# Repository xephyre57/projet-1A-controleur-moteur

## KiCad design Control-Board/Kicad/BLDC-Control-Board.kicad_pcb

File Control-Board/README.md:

# Carte de contrôle

## Objectif

Le but de cette carte de contrôle est de servir de cerveau que l'on vient plugger sur la carte de puissance adaptée au moteur que l'on souhaite contrôler. Cette connexion se fait via un [shield personalisé](#shield-de-connexion) qui permet de faire passer les signaux nécessaires entre les deux cartes ainsi que de les fixer ensemble. 

Cette carte de contrôle a été conçue autour d'un [STSPIN32G4](https://www.st.com/en/motor-drivers/stspin32g4.html) qui présente l'avantage d'avoir à la fois un microcontrôleur et un driver de mofsets intégré dans la même puce. Cela permet de réduire le nombre de composants nécessaires et ainsi d'avoir une carte plus compacte.

## Shématique de la carte de contrôle :

Le schéma de la carte de contrôle est disponible [ici](./Kicad/BLDC-Control-Board.kicad_sch), il a été séparé en 4 parties pour une meilleure lisibilité :
- [MCU & debug](#mcu--debug) : cette partie regroupe le microcontrôleur ainsi que tous les éléments nécessaires pour le faire fonctionner (oscillateur, capacités, pont diviseur de tension pour la programmation, etc.) ainsi que les diodes de debug.
- [Analog Sensing](#analog-sensing) : cette partie est dédiée à l'acquisition des signaux des capteurs de position (hall effect sensors) pour l'asservissement du moteur.
- [Communication](#communication) : cette partie regroupe les éléments nécessaires pour la communication extérieure (I2C, UART et CAN) ainsi que le ST-Link pour la programmation et le debug.
- [Connector](#connector) : cette partie contient les connecteurs et les point de fixation pour le [shield de connexion](#shield-de-connexion).

### MCU & debug

Cette première partie du schéma regroupe le microcontrôleur (en haut à gauche) ainsi que tous les éléments nécessaires pour le faire fonctionner (oscillateur, capacités, pont diviseur de tension pour la programmation, etc.) ainsi que les diodes de debug (en bas à gauche).

Pour le dimensionnement des différents éléments, nous avons suivi les recommandations de STMicroelectronics présentes dans la [datasheet du STSPIN32G4](https://www.st.com/resource/en/datasheet/stspin32g4.pdf) ainsi que dans les [application notes](https://www.st.com/en/motor-drivers/stspin32g4.html#documentation) associées.

### Analog Sensing

Dans cette partie du schéma, le but est de faire l'acquisition des signaux des capteurs de position (hall effect sensors) pour l'asservissement du moteur. Pour ce faire, nous avons utilisé les amplificateurs opérationnels intégrés dans le STSPIN32G4. Les amplificateurs opérationnels visibles sur le schéma si dessus ne sont donc pas des composants externes, ils sont simplement là afin d'aider à la lisibilité du schéma, par ailleurs afin d'éviter des erreurs lors du test du schéma, l'amplificateur opérationnel manquant du groupe de 4 ainsi que l'alimentation de ces amplificateurs opérationnels ont été dessinés dans le cadre en bas à gauche du schéma.

Par ailleurs, on peut remarquer sur le schéma que la boucle de retour sont barrée, sur le schéma, c'est du au fait que le logiciel que nous avons utilisé pour générer un code pour notre carte impose d'utilise une boucle de retour interne, nous n'avons donc pas peuplé ces composants et nous avons juste remplacer la résistance R_OP4_X par une soudure. Il est possible pour une prochaine version de la carte de retirer ces composants du PCB, cependant il peut être intéressant de les laisser car si on ne passe pas par le logiciel que l'on a utilisé pour générer le code, le fait d'avoir une boucle de retour externe permet d'avoir une plus grande flexibilité dans le choix de la configuration de la boucle de retour (la boucle de retour interne ne permet que de faire des puissance de 2).

### Communication

Cette partie du schéma regroupe les éléments lié à la communication extérieure. L'un des points du cahier des charges de cette carte était de faire une carte universelle qui à therme soit systématiquement utilisée lors que l'on a besoin de contrôler un moteur BDLC dans l'école. Dans ce cadre, il est nécessaire que la carte puisse communiquer avec la majorité des systèmes de contrôle, c'est pourquoi nous avons choisi d'intégrer à la fois une communication I2C, UART et CAN. 

D'autre part nous avons également intégré un connecteur pour le ST-Link avec les signaux nécessaires pour la programmation ainsi que ce nécessaire pour le debug afin de faciliter le développement sur la carte.

### Connector

## PCB

Pour le PCB il a été choisit de le faire en 4 couches afin de pouvoir réduire la taille de la carte tout en respectant les règles de routage. Le PCB a été conçu sur kicad et le fichier de conception est disponible [ici](./Kicad/BLDC-Control-Board.kicad_pcb).

### Répartition des couches
- Couches 1 (Top) contient tout les composants (à l'exception du connecteur avec la carte de puissance qui doit être situé sur la couche du dessous) ainsi que la majorité des pistes de signal.
- Couche 2 (GND) Cette couche est dédiée à la masse de la carte, aucune piste ne passe sur cette couche, les seul éléments présent sur cette couche sont le plan de masse ainsi que les vias.
- Couche 3 (Power) Cette couche est dédiée à l'alimentation de la carte, aucun plan de masse ne passe sur cette couche, Les deux circuits d'alimentation principaux de la carte (VM 24-48V et VBAT 3.3V) utilisent des plans d'alimentation sur cette couche plutôt que des pistes par ailleurs.
- Couche 4 (Bottom) Cette couche contient les pistes de signal qui ne pouvaient pas être routé sur la couche du dessus ainsi que le connecteur pour la carte de puissance qui doit être situé sur cette couche afin de pouvoir faire face à la carte de puissance.

### Largeur des pistes

Pour la largeur des pistes, nous avons séparé les pistes en deux catégories : 
- **les pistes de puissance** : cette catégorie regroupe toutes les pistes qui sont connectées au controleur de MOSFETs du STSPIN32G4, pour ces pistes, nous avons utilisé une largeur de 2 centièmes de pouce (0.508mm), cette largeur a été choisit en s'appuyant sur les largeurs de pistes utilisées par STMicroelectronics dans leur carte d'évaluation du STSPIN32G4 ([EVSPIN32G4](https://www.st.com/en/evaluation-tools/evspin32g4.html)). Cependant la largeur de piste est réduite à 1 centièmes de pouce (0.254mm) au abords de la puce car les pins du STSPIN32G4 sont trop rapprochées pour permettre une largeur de 2 centièmes de pouce.
- **les pistes de signal** : cette catégorie regroupe toutes les autre pistes (mise à part les pistes d'alimentation qui sont des plans d'alimentation), pour ces pistes, nous avons utilisé une largeur de 1 centièmes de pouce (0.254mm).

### isolation

Premièrement une isolation minimal de 0.2mm a été imposé entre toutes les pistes et les pads. Par ailleurs des tranchées d'isolation de 0.4mm traversant tout le PCB ont été ajoutées afin de lutter contre les problèmes de parasites. Ces tranchées d'isolation sont présentes entre les pistes de puissance et les pistes de signal ainsi qu'autour de l'oscillateur qui est une source de parasites importante.

Par ailleurs, conformément au recommandations de STMicroelectronics, au niveau du circuit d'alimentation et de régulation du STSPIN32G4, le PCB est vide sur toutes les couches à l'exception de la première couche ou seul les pistes nécessaires sont présentes, et remplacées par des zones afin d'augmenter la largeur des pistes.

### Shield de connexion

Pour créer une carte de puissance compatible avec cette carte de contrôle, il suffit d'utiliser le même connecteur (les signaux situés au même endroit) et de respecter la disposition suivantes pour les trous de fixation et le connecteur :

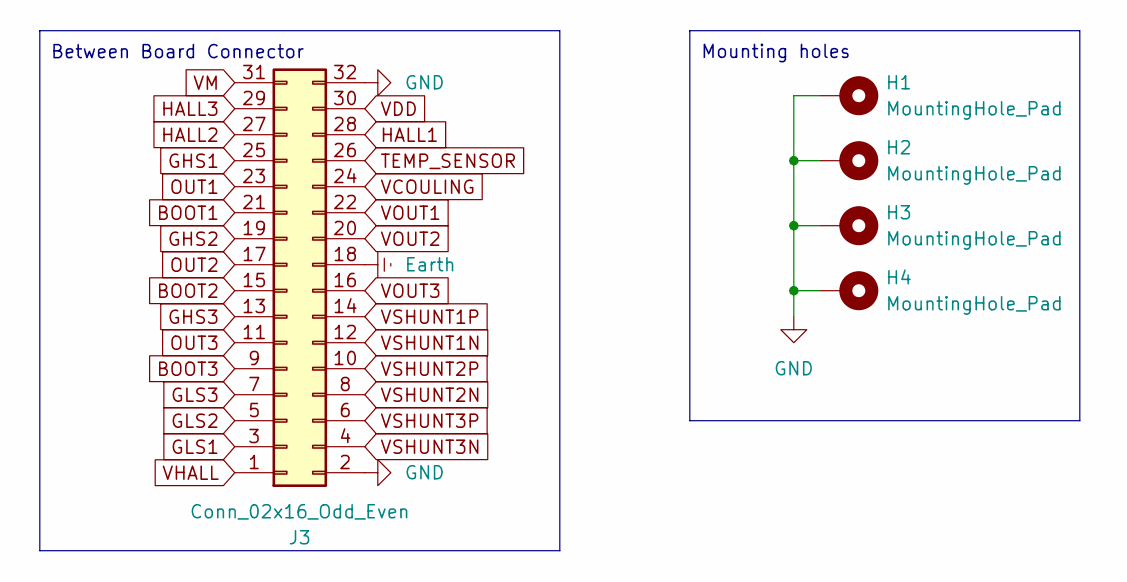
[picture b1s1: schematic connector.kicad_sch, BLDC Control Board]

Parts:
H1, H2, H3, H4: MountingHole_Pad; MountingHole_3.2mm_M3_DIN965_Pad
J3: Conn_02x16_Odd_Even; PinHeader_2x16_P2.54mm_Vertical

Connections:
BOOT1: J3.21; also elsewhere on the board
BOOT2: J3.15; also elsewhere on the board
BOOT3: J3.9; also elsewhere on the board
Earth: H1.1, H2.1, H3.1, H4.1, J3.2, J3.18, J3.32; also elsewhere on the board
GHS1: J3.25; also elsewhere on the board
GHS2: J3.19; also elsewhere on the board
GHS3: J3.13; also elsewhere on the board
GLS1: J3.3; also elsewhere on the board
GLS2: J3.5; also elsewhere on the board
GLS3: J3.7; also elsewhere on the board
HALL1: J3.28; also elsewhere on the board
HALL2: J3.27; also elsewhere on the board
HALL3: J3.29; also elsewhere on the board
OUT1: J3.23; also elsewhere on the board
OUT2: J3.17; also elsewhere on the board
OUT3: J3.11; also elsewhere on the board
TEMP_SENSOR: J3.26; also elsewhere on the board
VBAT: J3.30; also elsewhere on the board
VCOULING: J3.24; also elsewhere on the board
VHALL: J3.1; also elsewhere on the board
VM: J3.31; also elsewhere on the board
VOUT1: J3.22; also elsewhere on the board
VOUT2: J3.20; also elsewhere on the board
VOUT3: J3.16; also elsewhere on the board
VSHUNT1N: J3.12; also elsewhere on the board
VSHUNT1P: J3.14; also elsewhere on the board
VSHUNT2N: J3.8; also elsewhere on the board
VSHUNT2P: J3.10; also elsewhere on the board
VSHUNT3N: J3.4; also elsewhere on the board
VSHUNT3P: J3.6; also elsewhere on the board

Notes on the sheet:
Mounting holes
Between Board Connector

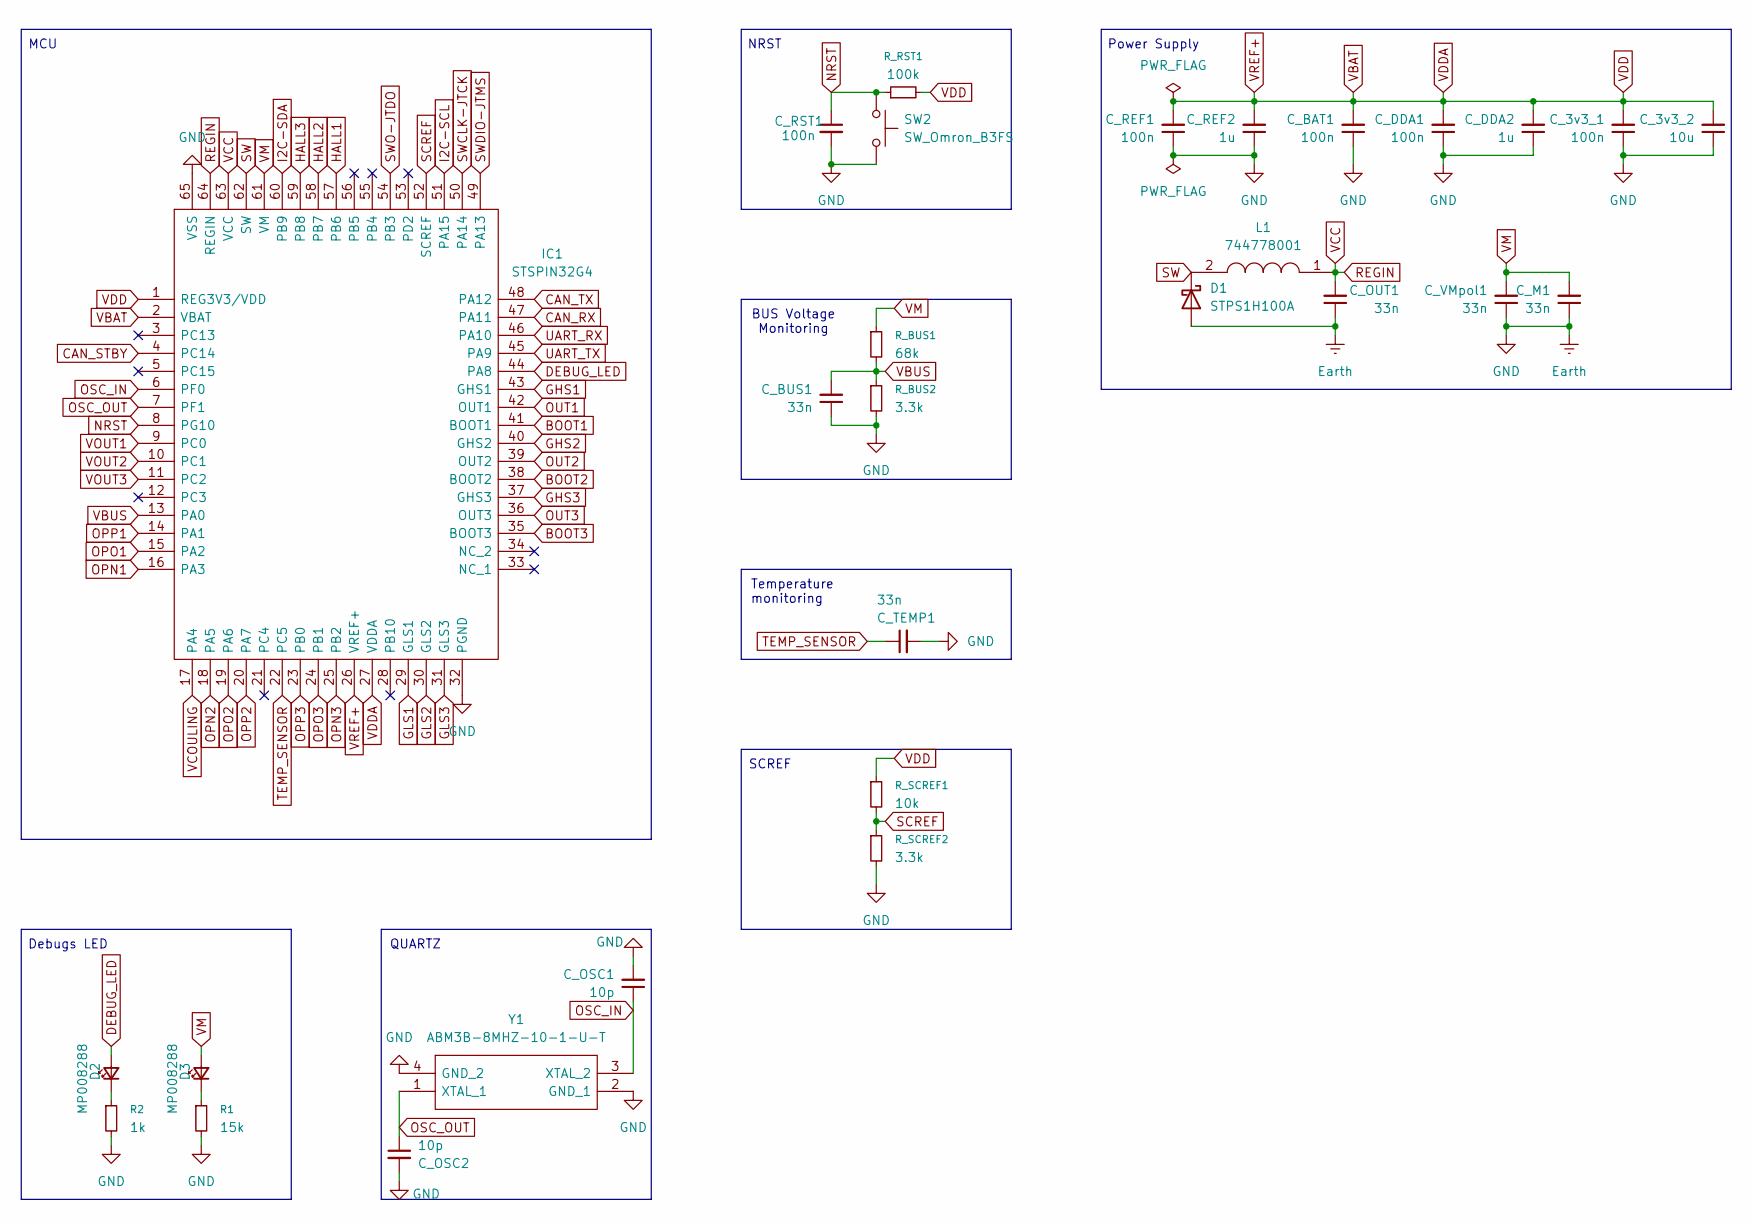
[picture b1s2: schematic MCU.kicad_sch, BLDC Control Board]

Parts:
C_3v3_1: 100n; C_0603_1608Metric_Pad1.08x0.95mm_HandSolder
C_3v3_2: 10u; C_0603_1608Metric_Pad1.08x0.95mm_HandSolder
C_BAT1: 100n; C_0603_1608Metric_Pad1.08x0.95mm_HandSolder
C_BUS1: 33n; C_0603_1608Metric_Pad1.08x0.95mm_HandSolder
C_DDA1: 100n; C_0603_1608Metric_Pad1.08x0.95mm_HandSolder
C_DDA2: 1u; C_0603_1608Metric_Pad1.08x0.95mm_HandSolder
C_M1: 33n; C_0603_1608Metric_Pad1.08x0.95mm_HandSolder
C_OSC1, C_OSC2: 10p; C_0603_1608Metric_Pad1.08x0.95mm_HandSolder
C_OUT1: 33n; C_0603_1608Metric_Pad1.08x0.95mm_HandSolder
C_REF1: 100n; C_0603_1608Metric_Pad1.08x0.95mm_HandSolder
C_REF2: 1u; C_0603_1608Metric_Pad1.08x0.95mm_HandSolder
C_RST1: 100n; C_0603_1608Metric_Pad1.08x0.95mm_HandSolder
C_TEMP1: 33n; C_0603_1608Metric_Pad1.08x0.95mm_HandSolder
C_VMpol1: 33n; C_0603_1608Metric_Pad1.08x0.95mm_HandSolder
D1: STPS1H100A; DIOM5126X265N
D2, D3: MP008288; LED_0603_1608Metric_Pad1.05x0.95mm_HandSolder
IC1: STSPIN32G4; QFN50P900X900X100-65N-D; Manufacturer_Part_Number STSPIN32G4; Mouser Part Number 511-STSPIN32G4
L1: 744778001; Manufacturer_Part_Number 744778001; Mouser Part Number 710-744778001
R1: 15k; R_0603_1608Metric_Pad0.98x0.95mm_HandSolder
R2: 1k; R_0603_1608Metric_Pad0.98x0.95mm_HandSolder
R_BUS1: 68k; R_0603_1608Metric_Pad0.98x0.95mm_HandSolder
R_BUS2: 3.3k; R_0603_1608Metric_Pad0.98x0.95mm_HandSolder
R_RST1: 100k; R_0603_1608Metric_Pad0.98x0.95mm_HandSolder
R_SCREF1: 10k; R_0603_1608Metric_Pad0.98x0.95mm_HandSolder
R_SCREF2: 3.3k; R_0603_1608Metric_Pad0.98x0.95mm_HandSolder
SW2: SW_Omron_B3FS; SW_SPST_Omron_B3FS-100xP
Y1: ABM3B-8MHZ-10-1-U-T; ABM3B; Manufacturer_Part_Number ABM3B-11.0592MHZ-10-1-U-T; Mouser Part Number 815-ABM3B-11.0592-T

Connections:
BOOT1: IC1.41 (BOOT1); also elsewhere on the board
BOOT2: IC1.38 (BOOT2); also elsewhere on the board
BOOT3: IC1.35 (BOOT3); also elsewhere on the board
CAN_RX: IC1.47 (PA11); also elsewhere on the board
CAN_STBY: IC1.4 (PC14); also elsewhere on the board
CAN_TX: IC1.48 (PA12); also elsewhere on the board
DEBUG_LED: D2.2 (A), IC1.44 (PA8)
Earth: C_3v3_1.1, C_3v3_2.1, C_BAT1.1, C_BUS1.1, C_DDA1.1, C_DDA2.1, C_M1.1, C_OSC1.2, C_OSC2.2, C_OUT1.1, C_REF1.1, C_REF2.1, C_RST1.2, C_TEMP1.2, C_VMpol1.1, D1.2 (A), IC1.32 (PGND), IC1.65 (VSS), R1.2, R2.2, R_BUS2.2, R_SCREF2.2, SW2.2, Y1.2 (GND_1), Y1.4 (GND_2); also elsewhere on the board
GHS1: IC1.43 (GHS1); also elsewhere on the board
GHS2: IC1.40 (GHS2); also elsewhere on the board
GHS3: IC1.37 (GHS3); also elsewhere on the board
GLS1: IC1.29 (GLS1); also elsewhere on the board
GLS2: IC1.30 (GLS2); also elsewhere on the board
GLS3: IC1.31 (GLS3); also elsewhere on the board
HALL1: IC1.57 (PB6); also elsewhere on the board
HALL2: IC1.58 (PB7); also elsewhere on the board
HALL3: IC1.59 (PB8); also elsewhere on the board
I2C-SCL: IC1.51 (PA15); also elsewhere on the board
I2C-SDA: IC1.60 (PB9); also elsewhere on the board
NRST: C_RST1.1, IC1.8 (PG10), R_RST1.1, SW2.1; also elsewhere on the board
unnamed: D2.1 (K), R2.1
unnamed: D3.1 (K), R1.1
OPN1: IC1.16 (PA3); also elsewhere on the board
OPN2: IC1.18 (PA5); also elsewhere on the board
OPN3: IC1.25 (PB2); also elsewhere on the board
OPO1: IC1.15 (PA2); also elsewhere on the board
OPO2: IC1.19 (PA6); also elsewhere on the board
OPO3: IC1.24 (PB1); also elsewhere on the board
OPP1: IC1.14 (PA1); also elsewhere on the board
OPP2: IC1.20 (PA7); also elsewhere on the board
OPP3: IC1.23 (PB0); also elsewhere on the board
OSC_IN: C_OSC1.1, IC1.6 (PF0), Y1.3 (XTAL_2)
OSC_OUT: C_OSC2.1, IC1.7 (PF1), Y1.1 (XTAL_1)
OUT1: IC1.42 (OUT1); also elsewhere on the board
OUT2: IC1.39 (OUT2); also elsewhere on the board
OUT3: IC1.36 (OUT3); also elsewhere on the board
REGIN: C_OUT1.2, IC1.63 (VCC), IC1.64 (REGIN), L1.1; also elsewhere on the board
SCREF: IC1.52 (SCREF), R_SCREF1.2, R_SCREF2.1
SW: D1.1 (K), IC1.62 (SW), L1.2
SWCLK-JTCK: IC1.50 (PA14); also elsewhere on the board
SWDIO-JTMS: IC1.49 (PA13); also elsewhere on the board
SWO-JTDO: IC1.54 (PB3); also elsewhere on the board
TEMP_SENSOR: C_TEMP1.1, IC1.22 (PC5); also elsewhere on the board
UART_RX: IC1.46 (PA10); also elsewhere on the board
UART_TX: IC1.45 (PA9); also elsewhere on the board
VBAT: C_3v3_1.2, C_3v3_2.2, C_BAT1.2, C_DDA1.2, C_DDA2.2, C_REF1.2, C_REF2.2, IC1.1 (REG3V3/VDD), IC1.2 (VBAT), IC1.26 (VREF+), IC1.27 (VDDA), R_RST1.2, R_SCREF1.1; also elsewhere on the board
VBUS: C_BUS1.2, IC1.13 (PA0), R_BUS1.2, R_BUS2.1
VCOULING: IC1.17 (PA4); also elsewhere on the board
VM: C_M1.2, C_VMpol1.2, D3.2 (A), IC1.61 (VM), R_BUS1.1; also elsewhere on the board
VOUT1: IC1.9 (PC0); also elsewhere on the board
VOUT2: IC1.10 (PC1); also elsewhere on the board
VOUT3: IC1.11 (PC2); also elsewhere on the board

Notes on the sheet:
QUARTZ
NRST
BUS Voltage Monitoring
Debugs LED
Power Supply
SCREF
MCU
Temperature monitoring

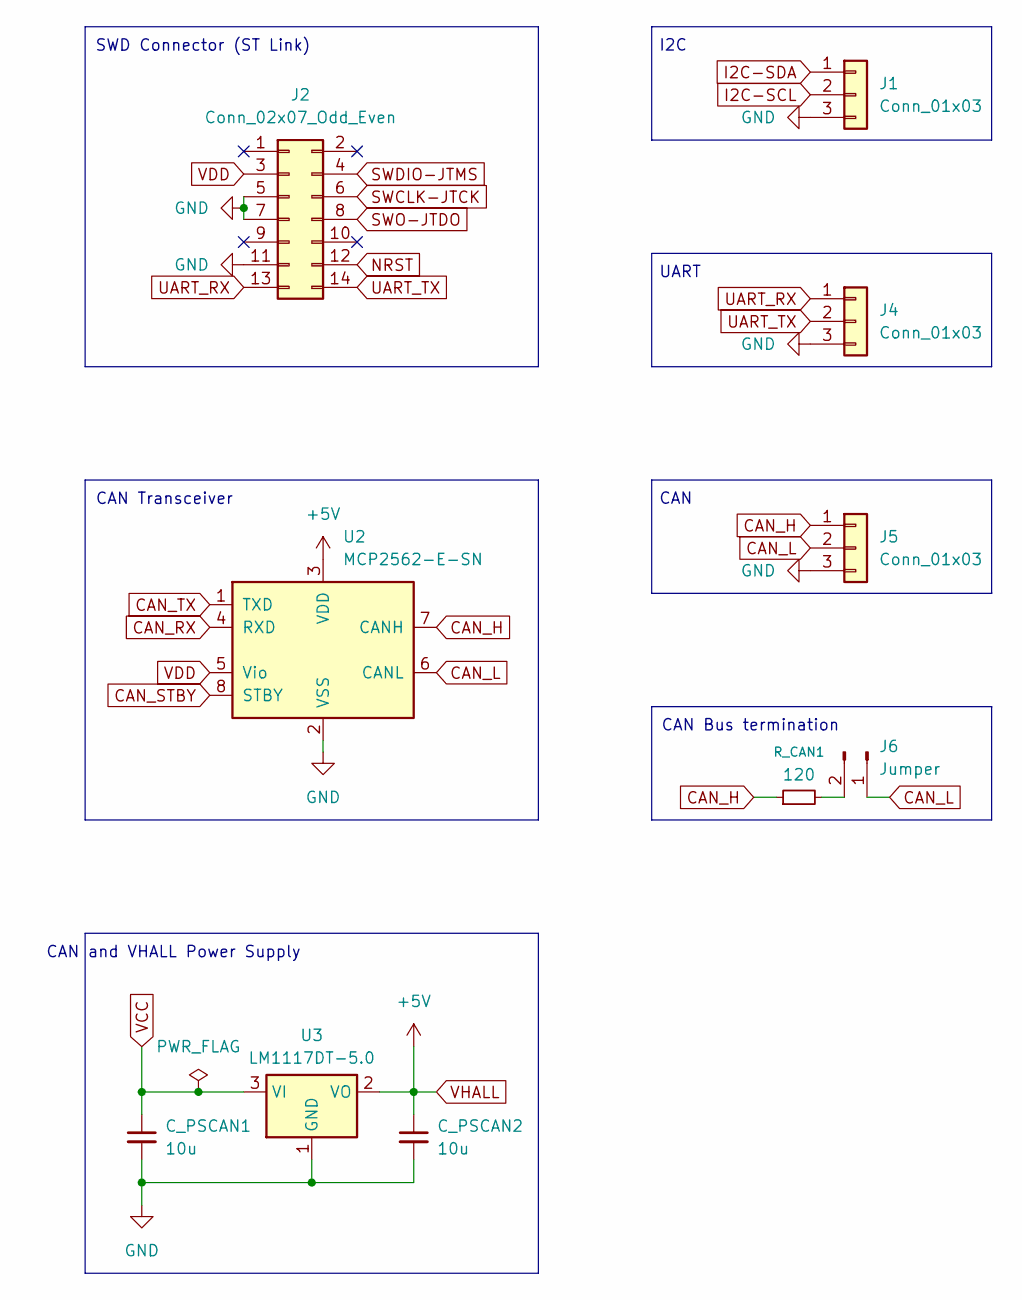
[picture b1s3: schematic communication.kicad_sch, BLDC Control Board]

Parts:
C_PSCAN1, C_PSCAN2: 10u; C_0603_1608Metric_Pad1.08x0.95mm_HandSolder
J1, J4, J5: Conn_01x03; JST_XH_B3B-XH-A_1x03_P2.50mm_Vertical
J2: Conn_02x07_Odd_Even; PinHeader_2x07_P2.54mm_Vertical_SMD
J6: Jumper; PinHeader_1x02_P2.54mm_Vertical
R_CAN1: 120; R_0603_1608Metric_Pad0.98x0.95mm_HandSolder
U2: MCP2562-E-SN; SOIC-8_3.9x4.9mm_P1.27mm
U3: LM1117DT-5.0; TO-252-3_TabPin2

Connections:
CAN_H: J5.1, R_CAN1.1, U2.7 (CANH)
CAN_L: J5.2, J6.1, U2.6 (CANL)
CAN_RX: U2.4 (RXD); also elsewhere on the board
CAN_STBY: U2.8 (STBY); also elsewhere on the board
CAN_TX: U2.1 (TXD); also elsewhere on the board
Earth: C_PSCAN1.2, C_PSCAN2.2, J1.3, J2.5, J2.7, J2.11, J4.3, J5.3, U2.2 (VSS), U3.1 (GND); also elsewhere on the board
I2C-SCL: J1.2; also elsewhere on the board
I2C-SDA: J1.1; also elsewhere on the board
NRST: J2.12; also elsewhere on the board
unnamed: J6.2, R_CAN1.2
REGIN: C_PSCAN1.1, U3.3 (VI); also elsewhere on the board
SWCLK-JTCK: J2.6; also elsewhere on the board
SWDIO-JTMS: J2.4; also elsewhere on the board
SWO-JTDO: J2.8; also elsewhere on the board
UART_RX: J2.13, J4.1; also elsewhere on the board
UART_TX: J2.14, J4.2; also elsewhere on the board
VBAT: J2.3, U2.5 (Vio); also elsewhere on the board
VHALL: C_PSCAN2.1, U2.3 (VDD), U3.2 (VO); also elsewhere on the board

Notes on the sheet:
CAN Transceiver
CAN
CAN Bus termination
I2C
UART
SWD Connector (ST Link)
CAN and VHALL Power Supply

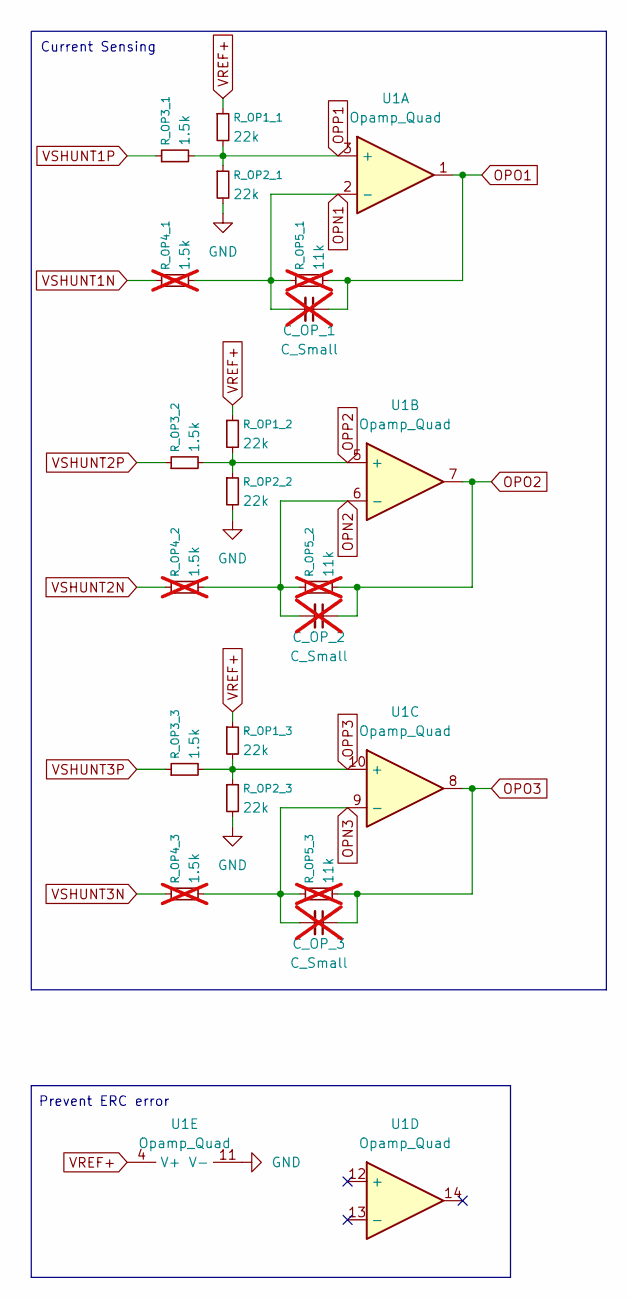
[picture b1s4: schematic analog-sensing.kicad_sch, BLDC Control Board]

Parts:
C_OP_1, C_OP_2, C_OP_3: C_Small; C_0603_1608Metric_Pad1.08x0.95mm_HandSolder; not fitted
R_OP1_1, R_OP1_2, R_OP1_3, R_OP2_1, R_OP2_2, R_OP2_3: 22k; R_0603_1608Metric_Pad0.98x0.95mm_HandSolder
R_OP3_1, R_OP3_2, R_OP3_3: 1.5k; R_0603_1608Metric_Pad0.98x0.95mm_HandSolder
R_OP4_1, R_OP4_2, R_OP4_3: 1.5k; R_0603_1608Metric_Pad0.98x0.95mm_HandSolder; not fitted
R_OP5_1, R_OP5_2, R_OP5_3: 11k; R_0603_1608Metric_Pad0.98x0.95mm_HandSolder; not fitted
U1: Opamp_Quad

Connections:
Earth: R_OP2_1.2, R_OP2_2.2, R_OP2_3.2, U1.11 (V-); also elsewhere on the board
OPN1: C_OP_1.2, R_OP4_1.2, R_OP5_1.1, U1.2 (-); also elsewhere on the board
OPN2: C_OP_2.2, R_OP4_2.2, R_OP5_2.1, U1.6 (-); also elsewhere on the board
OPN3: C_OP_3.2, R_OP4_3.2, R_OP5_3.1, U1.9 (-); also elsewhere on the board
OPO1: C_OP_1.1, R_OP5_1.2, U1.1; also elsewhere on the board
OPO2: C_OP_2.1, R_OP5_2.2, U1.7; also elsewhere on the board
OPO3: C_OP_3.1, R_OP5_3.2, U1.8; also elsewhere on the board
OPP1: R_OP1_1.2, R_OP2_1.1, R_OP3_1.2, U1.3 (+); also elsewhere on the board
OPP2: R_OP1_2.2, R_OP2_2.1, R_OP3_2.2, U1.5 (+); also elsewhere on the board
OPP3: R_OP1_3.2, R_OP2_3.1, R_OP3_3.2, U1.10 (+); also elsewhere on the board
VBAT: R_OP1_1.1, R_OP1_2.1, R_OP1_3.1, U1.4 (V+); also elsewhere on the board
VSHUNT1N: R_OP4_1.1; also elsewhere on the board
VSHUNT1P: R_OP3_1.1; also elsewhere on the board
VSHUNT2N: R_OP4_2.1; also elsewhere on the board
VSHUNT2P: R_OP3_2.1; also elsewhere on the board
VSHUNT3N: R_OP4_3.1; also elsewhere on the board
VSHUNT3P: R_OP3_3.1; also elsewhere on the board

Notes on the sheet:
Current Sensing
Prevent ERC error

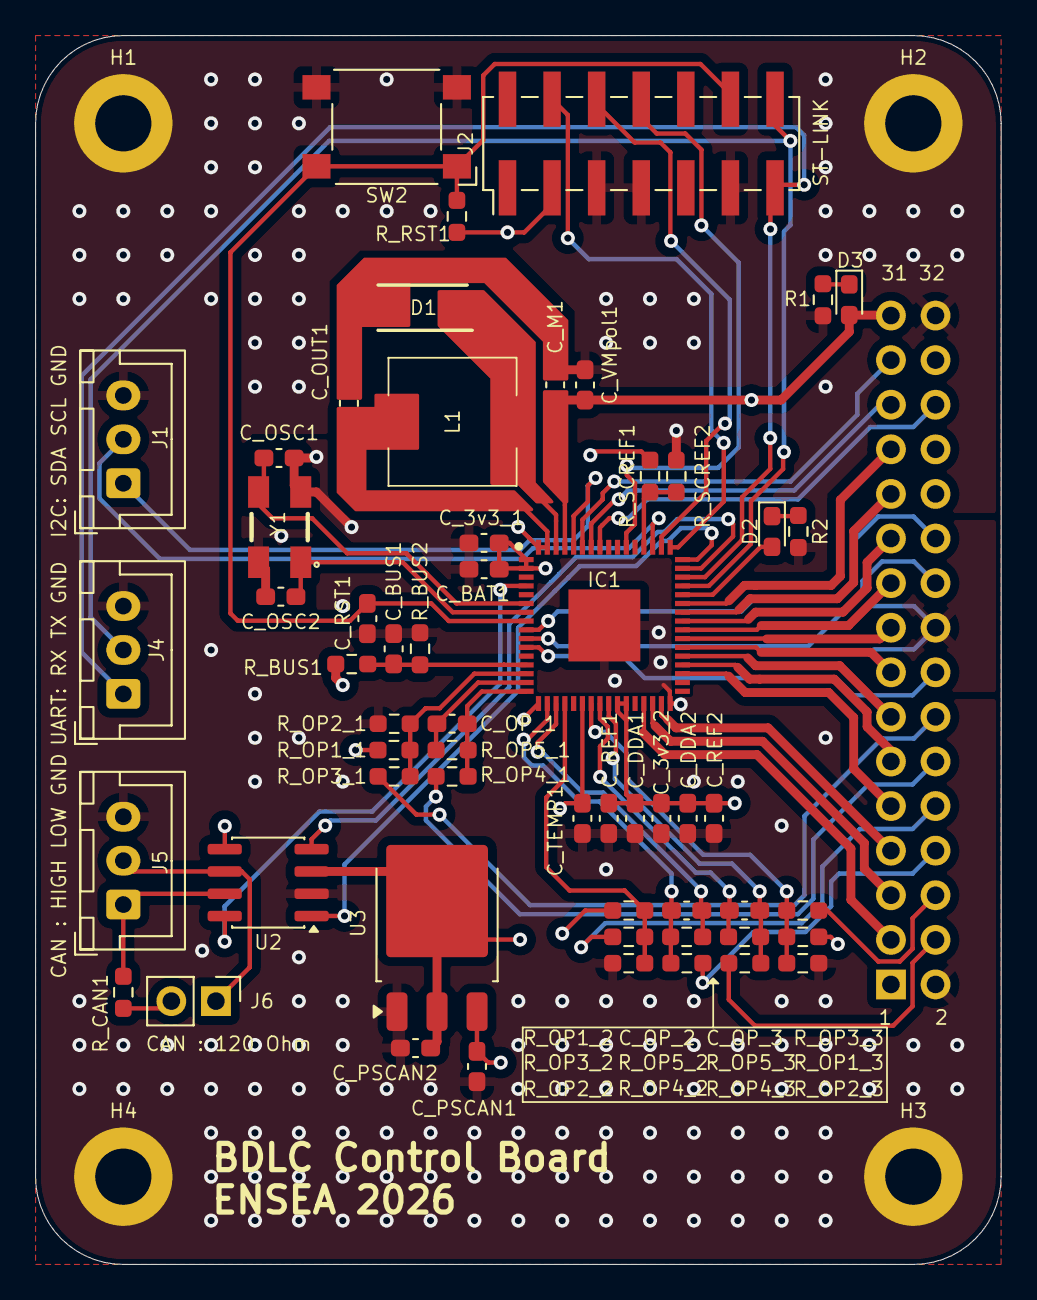
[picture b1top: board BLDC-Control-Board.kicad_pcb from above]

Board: 4 copper layers, 55.0 x 70.0 mm, 62 parts (1 on the bottom side), 62 nets.

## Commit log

2026-02-02 Ajout des premiers fichiers de documentation
2026-05-30 Add control board doc
    - Control Board Schematic file
    - Control Board PCB file
    - Control Board Documentation
2026-05-30 ajout de la partie software et du dimensionnement des composants du Control Board
2026-05-30 Suppression d'un fichier en trop
